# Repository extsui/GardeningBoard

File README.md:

# GardeningBoard
## 概要
- ガーデニングボードは着脱可能基板を自由に抜き差しして自分好みの作品を生み出せるというコンセプトの作品です。
- 当初はガーデニングにちなんで庭関連の基板ばかり作っていましたが、現在はガーデニングという手法をベースにした表現に概念を拡張しています。
  - 系譜：KawaiiMakeMyBoard --> GardeningBoard --> Fountain

## 基板
| 基板名   | 形状                  | 概要                                                                                      | 組み上げ対象作品       |
|----------|-----------------------|-------------------------------------------------------------------------------------------|------------------------|
| Grass    | 草                    | 挿入部品                                                                                  | GardeningBoard 等      |
| Tree     | 木                    | 挿入部品                                                                                  | GardeningBoard 等      |
| House    | 家                    | 挿入部品                                                                                  | GardeningBoard 等      |
| Land     | 正方形 (旧式)・上部側 | 挿入部品用穴付き・半田接合式                                                              | KawaiiMakeMyBoard 専用 |
| Base     | 正方形 (旧式)・下部側 | カードエッジコネクタ土台                                                                  | KawaiiMakeMyBoard 専用 |
| Tile     | 正六角形・上部側      | 挿入部品用穴付き                                                                          | GardeningBoard 等      |
| Ground   | 正六角形・下部側      | STM32F303 使用、Pillar からの信号を挿入分に分配<br>STM 未実装を Base の代わりとしても使用 | GardeningBoard 専用    |
| Pillar   | 正六角形・最下部側    | SeeduinoXIAO 使用、単体動作可、GardeningBoard 制御の最上位                                | GardeningBoard 専用    |
| Building | 縦長長方形・挿入部品  | 7セグ6桁x6行、GardeningBoard と互換性無し                                                 | 新規                   |
| Fountain | 正六角形・下部側      | XIAO-ESP32C3 使用、Building・Tile 想定                                                    | 新規                   |

※順番は開発順

## プログラム
- Firmware/Balan
  - Ground に搭載されている STM32F303 向けのプログラム
  - 上位 I2C から受け取ったデータ (点灯パターン等) を元に、下位 I2C に接続されている HT16K33 を制御する
- M5Stack/Pump
  - PC から USB シリアル経由で受信したデータを Balan に送信する M5Stack 向けのプログラム
  - Balan への送信は I2C に変換して GROVE ケーブル経由で行う
  - GardeningBoard 開発時向けに使用したもので、GardeningBoard 最終系には含まれていない
- Tools/PruningTool
  - Pump と対応する PC 側の制御ツール (C# フォームアプリ)
  - 草/木/家/土等の基本パーツ一つ一つの点灯パターン作成・検討に使用
- Seeedino/Pillar
  - Pillar 基板に搭載されている SeeeduinoXIAO 向けのプログラム
  - PC から USB シリアル経由で受信したデータを Balan に送信する (Pump と立ち位置は似ている)
  - スタンドアローン動作も想定している
  - Pillar 基板に搭載されている以下を制御する
    - タクトスイッチ (状態遷移用)
    - DFPlayerMp3 基板 (音楽再生用)
    - microSD (点灯表示シナリオ読み込み用)
    - ボリューム2個 (輝度調整・表示周期変更用)
    - I2C マスタ GROVE コネクタ (Balan への信号用)
    - 0.96 inch I2C 有機 EL グラフィックス表示器 (各種情報表示用)
- Tools/Sprinkler
  - Pillar と対応する PC 側の制御ツール (C# WPF)
  - PruningTool のように基本パーツの点灯パターン検討も出来なくはないが、<br>Sprinkler はどちらかというと点灯パターンを組み合わせた GardeningBoard 全体の表示シナリオ検討・作成に使用することを想定
  - 表示シナリオ検討は以下の手順で行う
    - GardeningBoard (Pillar) と接続する
    - リアルタイム制御用のテキストボックスにフォーカスを当てた状態にする
    - キーボードのキーそれぞれに各パーツと表示パターンが割り当ててあるので自由にキー入力する
  - 作成した表示シナリオを Pillar で再生できる形式に変換・ファイル出力できる (ハズ)
- Tools/PatternConverter
  - 基本パーツの複雑な点灯パターン検討・作成用の Python スクリプト
  - 点灯パターンは yml ファイルで定義し、以下の二つに変換する
    - C/C++ 形式 (Balan のプログラムに埋め込む用)
    - C# 形式 (Sprinkler のシナリオ検討で点灯パターンを入力補完するためのパターン enum 定義用)
- Tools/BuildingPainter
  - TODO:

※順番は開発順

## 代表的な構成
### KawaiiMakeMyBoard 
| 基板名 | 個数 |
|--------|------|
| Grass  | 2    |
| Tree   | 1    |
| Land   | 1    |
| Base   | 1    |

### GardeningBoard
| 基板名 | 個数 | 備考                        |
|--------|------|-----------------------------|
| Grass  | 3    | 手前側に3個                 |
| Tree   | 3    | 奥側に3個                   |
| House  | 1    | 中央に1個                   |
| Tile   | 7    | -                           |
| Ground | 7    | STM 実装は2個、残りは中継用 |
| Pillar | 1    | 中央基板のさらに下に配置    |

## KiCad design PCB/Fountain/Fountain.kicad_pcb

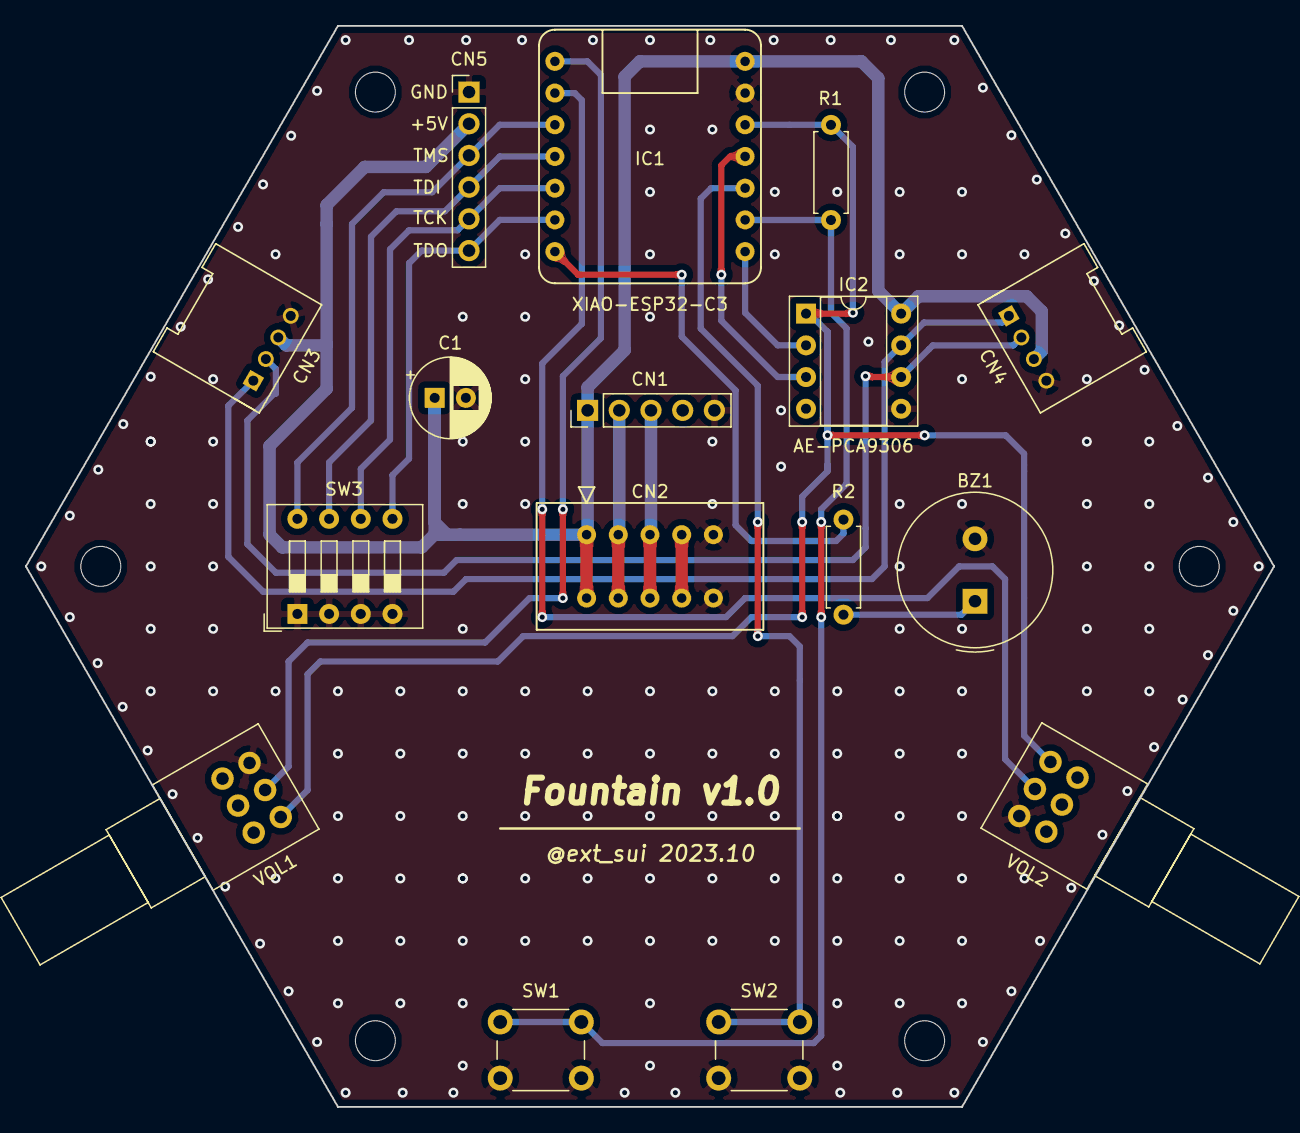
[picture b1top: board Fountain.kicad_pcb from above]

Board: 2 copper layers, 100.0 x 86.6 mm, 22 parts (0 on the bottom side), 17 nets.

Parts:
BZ1: Buzzer; Buzzer_TDK_PS1240P02BT_D12.2mm_H6.5mm
C1: CP; CP_Radial_D6.3mm_P2.50mm
CN1: Conn_01x05_Female; PinHeader_1x05_P2.54mm_Vertical
CN2: CardEdgeConnector5P; CONN_CARD_EDGE_395-010-521-201
CN3, CN4: GROVE_IIC_5V; HW4-2.0-90D
CN5: JTAG; PinHeader_1x06_P2.54mm_Vertical
H1, H2, H3, H4, H5, H6: MountingHole; MountingHole_3.2mm_M3
IC1: XIAO-ESP32-C3; SeeeduinoXIAO
IC2: AE-PCA9306; DIP-8_W7.62mm_Socket
R1: 10k; R_Axial_DIN0207_L6.3mm_D2.5mm_P7.62mm_Horizontal
R2: 1k; R_Axial_DIN0207_L6.3mm_D2.5mm_P7.62mm_Horizontal
SW1, SW2: (TBD); SW_PUSH_6mm_H8.5mm
SW3: DIPSW-4P; SW_DIP_SPSTx04_Slide_9.78x12.34mm_W7.62mm_P2.54mm
VOL1, VOL2: (TBD); Potentiometer_Alps_RK097_Dual_Horizontal

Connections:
3V3: IC1.12, IC2.1, R1.2, VOL1.6, VOL2.6
5V: C1.1, CN1.1, CN2.1, CN3.3, CN4.3, CN5.2, IC1.14, IC2.8
GND: BZ1.2, C1.2, CN1.5, CN2.5, CN3.4, CN4.4, CN5.1, IC1.13, IC2.5, SW1.2, SW2.2, SW3.1, SW3.2, SW3.3, SW3.4, VOL1.4, VOL2.4
unnamed: BZ1.1, R2.2
unnamed: CN5.3, IC1.3, SW3.8
unnamed: CN5.4, IC1.4, SW3.7
unnamed: CN5.5, IC1.5, SW3.6
unnamed: CN5.6, IC1.6, SW3.5
unnamed: IC1.7, R2.1
unnamed: IC1.9, R1.1, SW1.1
unnamed: IC1.10, SW2.1
RV1: IC1.1, VOL1.5
RV2: IC1.2, VOL2.5
SCL_3V3: IC1.8, IC2.2
SCL_5V: CN1.3, CN2.3, CN3.1, CN4.1, IC2.7
SDA_3V3: IC1.11, IC2.3
SDA_5V: CN1.2, CN2.2, CN3.2, CN4.2, IC2.6

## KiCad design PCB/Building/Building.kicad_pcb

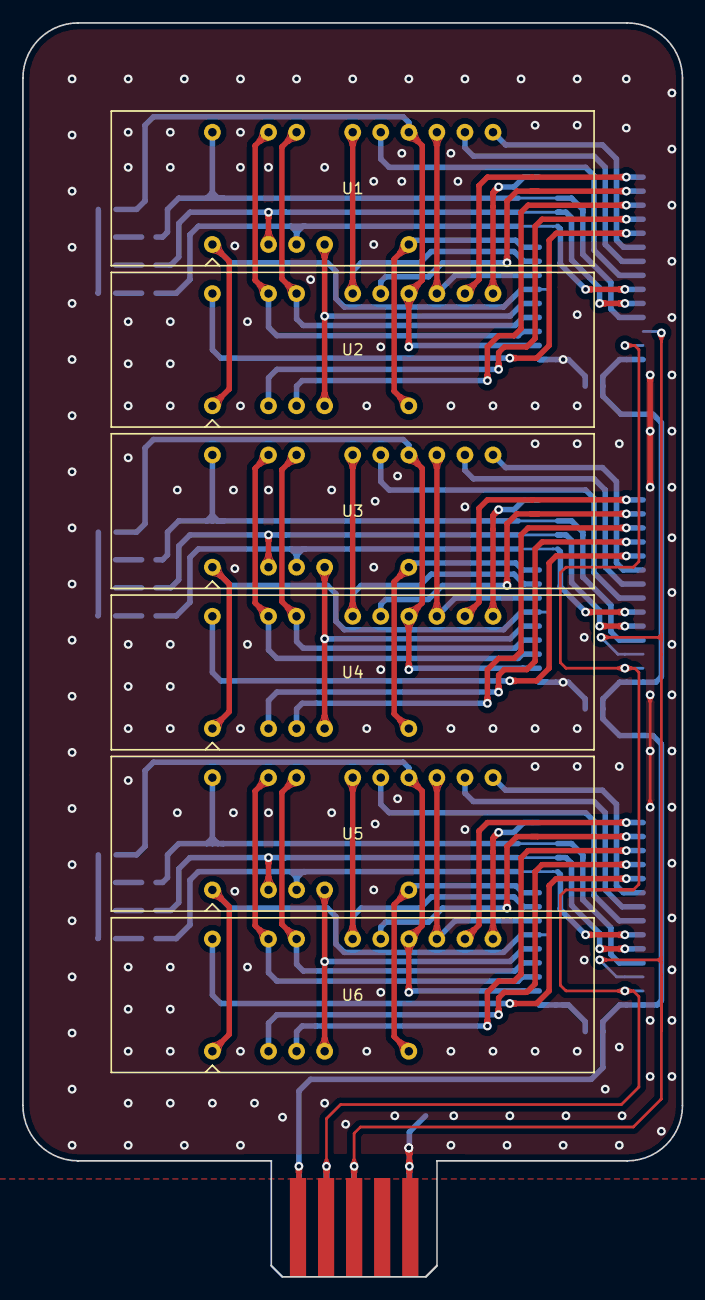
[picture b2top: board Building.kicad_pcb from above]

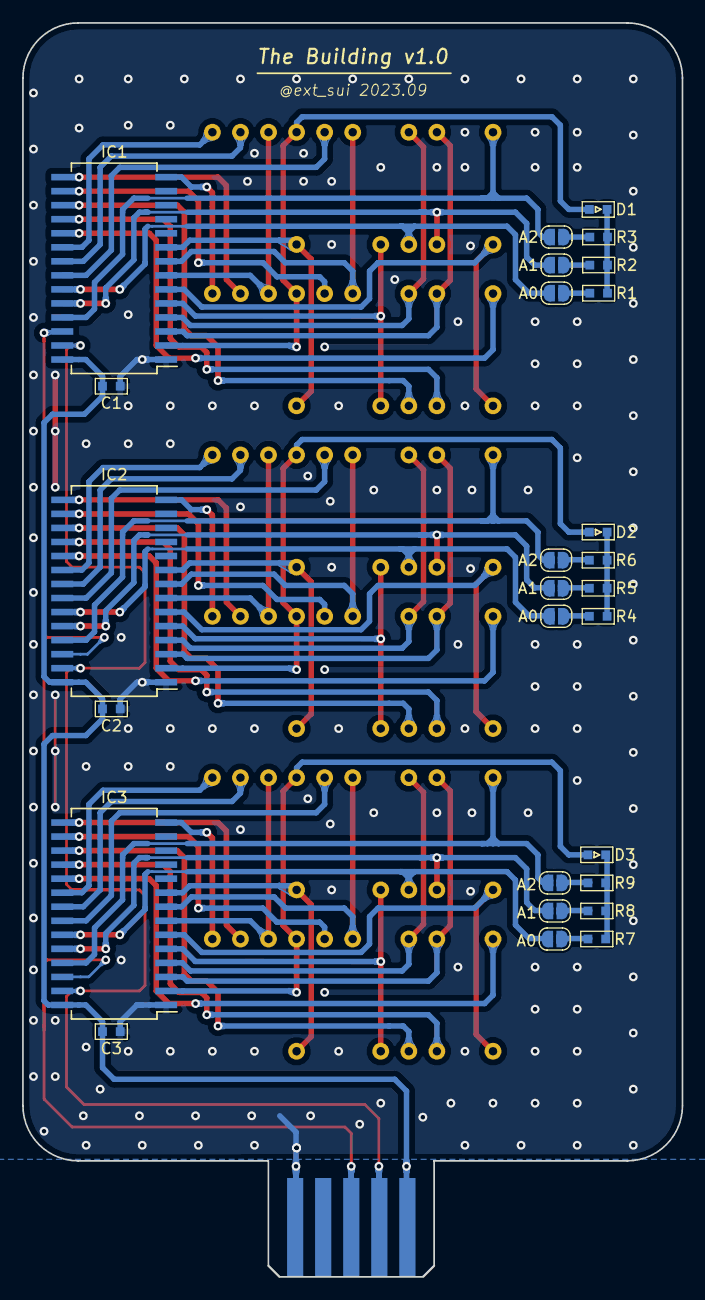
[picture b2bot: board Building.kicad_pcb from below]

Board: 2 copper layers, 59.6 x 113.5 mm, 34 parts (27 on the bottom side), 76 nets.

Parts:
C1, C2, C3: 0.1u; C_1608_HandSolderingCustom
D1, D2, D3: D; LED_1608_HandSolderingCustom
IC1, IC2, IC3: HT16K33-28SOP; SOIC-28W_7.5x18.7mm_P1.27mm
J1: Conn_01x05; EDAC_5P_P2.54mm
JP1, JP4, JP7: A0; SolderJumper-2_P1.3mm_Open_RoundedPad1.0x1.5mm
JP2, JP5, JP8: A1; SolderJumper-2_P1.3mm_Open_RoundedPad1.0x1.5mm
JP3, JP6, JP9: A2; SolderJumper-2_P1.3mm_Open_RoundedPad1.0x1.5mm
R1, R2, R3, R4, R5, R6, R7, R8, R9: 39k; R_1608_HandSolderingCustom
U1, U2, U3, U4, U5, U6: OSL60362_IX; OSL60362_XX

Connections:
+5V: C1.1, C2.1, C3.1, IC1.28, IC2.28, IC3.28, J1.1
/A_1: D1.2, IC1.2, U1.15, U2.15
/A_2: D2.2, IC2.2, U3.15, U4.15
/A_3: D3.2, IC3.2, U5.15, U6.15
/B_1: IC1.3, U1.20, U2.20
/B_2: IC2.3, U3.20, U4.20
/B_3: IC3.3, U5.20, U6.20
/CA1: IC1.25, JP3.2, U1.22
/CA2: IC1.24, JP2.2, U1.3
/CA3: IC1.23, JP1.2, U1.4
/CA4: IC1.22, U1.16
/CA5: IC1.21, U1.13
/CA6: IC1.20, U1.12
/CA7: IC1.19, U2.22
/CA8: IC1.18, U2.3
/CA9: IC1.17, U2.4
/CA10: IC1.16, U2.16
/CA11: IC1.15, U2.13
/CA12: IC1.14, U2.12
/CA13: IC2.25, JP6.2, U3.22
/CA14: IC2.24, JP5.2, U3.3
/CA15: IC2.23, JP4.2, U3.4
/CA16: IC2.22, U3.16
/CA17: IC2.21, U3.13
/CA18: IC2.20, U3.12
/CA19: IC2.19, U4.22
/CA20: IC2.18, U4.3
/CA21: IC2.17, U4.4
/CA22: IC2.16, U4.16
/CA23: IC2.15, U4.13
/CA24: IC2.14, U4.12
/CA25: IC3.25, JP9.2, U5.22
/CA26: IC3.24, JP8.2, U5.3
/CA27: IC3.23, JP7.2, U5.4
/CA28: IC3.22, U5.16
/CA29: IC3.21, U5.13
/CA30: IC3.20, U5.12
/CA31: IC3.19, U6.22
/CA32: IC3.18, U6.3
/CA33: IC3.17, U6.4
/CA34: IC3.16, U6.16
/CA35: IC3.15, U6.13
/CA36: IC3.14, U6.12
/C_1: IC1.4, U1.19, U2.19
/C_2: IC2.4, U3.19, U4.19
/C_3: IC3.4, U5.19, U6.19
/DP_1: IC1.9, U1.8, U2.8
/DP_2: IC2.9, U3.8, U4.8
/DP_3: IC3.9, U5.8, U6.8
/D_1: IC1.5, U1.5, U2.5
/D_2: IC2.5, U3.5, U4.5
/D_3: IC3.5, U5.5, U6.5
/E_1: IC1.6, U1.1, U2.1
/E_2: IC2.6, U3.1, U4.1
/E_3: IC3.6, U5.1, U6.1
/F_1: IC1.7, U1.14, U2.14
/F_2: IC2.7, U3.14, U4.14
/F_3: IC3.7, U5.14, U6.14
/G_1: IC1.8, U1.17, U2.17
/G_2: IC2.8, U3.17, U4.17
/G_3: IC3.8, U5.17, U6.17
GND: C1.2, C2.2, C3.2, IC1.1, IC2.1, IC3.1, J1.5
unnamed: D1.1, R1.2, R2.2, R3.2
unnamed: D2.1, R4.2, R5.2, R6.2
unnamed: D3.1, R7.2, R8.2, R9.2
unnamed: JP1.1, R1.1
unnamed: JP2.1, R2.1
unnamed: JP3.1, R3.1
unnamed: JP4.1, R4.1
unnamed: JP5.1, R5.1
unnamed: JP6.1, R6.1
unnamed: JP7.1, R7.1
unnamed: JP8.1, R8.1
unnamed: JP9.1, R9.1
SCL: IC1.26, IC2.26, IC3.26, J1.3
SDA: IC1.27, IC2.27, IC3.27, J1.2

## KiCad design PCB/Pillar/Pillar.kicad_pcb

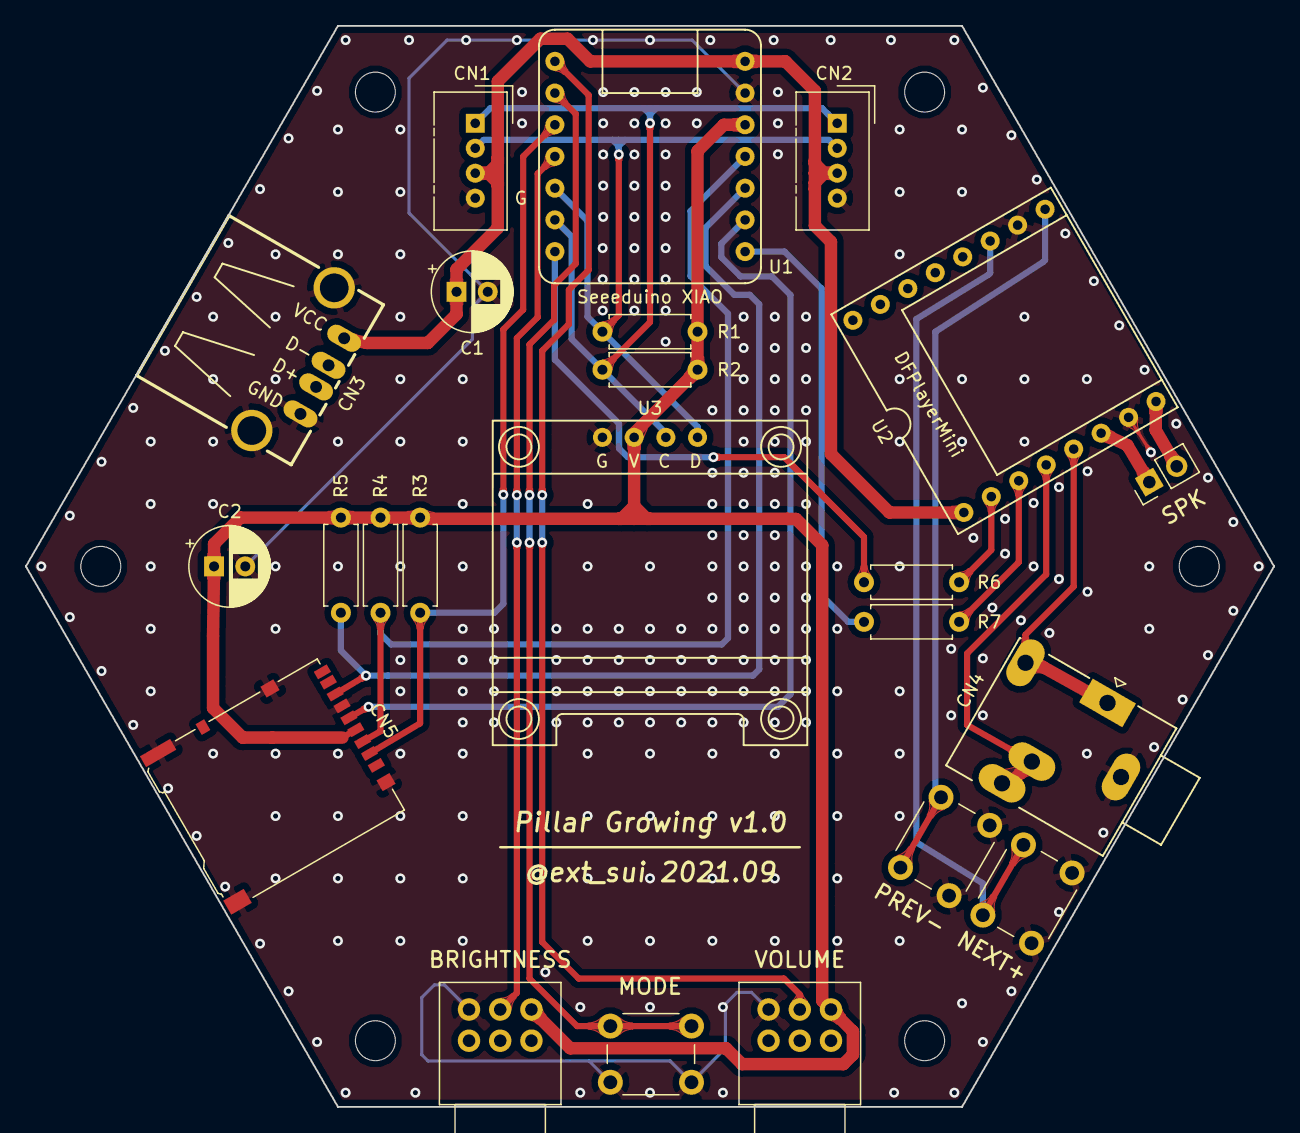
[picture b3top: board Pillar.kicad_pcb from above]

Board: 2 copper layers, 100.0 x 86.6 mm, 29 parts (0 on the bottom side), 22 nets.

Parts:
C1, C2: 100u; CP_Radial_D6.3mm_P2.50mm
CN1, CN2: GROVE_IIC_5V; NS-Tech_Grove_1x04_P2mm_Vertical
CN3: USB_A; USB4+2P-2.0-90D
CN4: AudioJack3_SwitchTR; Jack_3.5mm_Ledino_KB3SPRS_Horizontal
CN5: Micro_SD_Card_Det_Hirose_DM3AT; microSD_HC_Hirose_DM3AT-SF-PEJM5
H1, H2, H3, H4, H5, H6: MountingHole; MountingHole_3.2mm_M3
J1: Speaker; PinHeader_1x02_P2.54mm_Vertical
R1, R2, R3, R4, R5: 4.7k; R_Axial_DIN0207_L6.3mm_D2.5mm_P7.62mm_Horizontal
R6, R7: 1k; R_Axial_DIN0207_L6.3mm_D2.5mm_P7.62mm_Horizontal
RV1: BRIGHTNESS; Potentiometer_Alps_RK097_Dual_Horizontal
RV2: VOLUME; Potentiometer_Alps_RK097_Dual_Horizontal
SW1: MDOE; SW_PUSH_6mm_H8.5mm
SW2: NEXT/VOL+; SW_PUSH_6mm_H8.5mm
SW3: PREV/VOL-; SW_PUSH_6mm_H8.5mm
U1: SeeeduinoXIAO
U2: DFPlayerMini
U3: OLED_128x64_IIC; OLED_128x64_0.96inch

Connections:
3V3: C2.1, CN5.4, R1.1, R2.1, R3.1, R4.1, R5.1, RV1.6, RV2.6, U1.12, U3.2
5V: C1.1, CN1.3, CN2.3, CN3.1, U1.14, U2.1
CS: CN5.2, R3.2, U1.3
GND: C1.2, C2.2, CN1.4, CN2.4, CN3.4, CN3.5, CN4.S, CN5.6, CN5.11, RV1.4, RV2.4, SW1.2, SW2.2, SW3.2, U1.13, U2.7, U2.10, U3.1
MISO: CN5.7, R5.2, U1.10
MOSI: CN5.3, R4.2, U1.11
unnamed: CN4.R, CN4.RN, U2.4
unnamed: CN4.T, CN4.TN, U2.5
unnamed: J1.1, U2.6
unnamed: J1.2, U2.8
unnamed: R6.1, U2.2
unnamed: R7.1, U2.3
unnamed: SW1.1, U1.2
unnamed: SW2.1, U2.11
unnamed: SW3.1, U2.9
RV_B: RV1.5, U1.4
RV_V: RV2.5, U1.1
RXD: R7.2, U1.8
SCK: CN5.5, U1.9
SCL: CN1.1, CN2.1, R2.2, U1.6, U3.3
SDA: CN1.2, CN2.2, R1.2, U1.5, U3.4
TXD: R6.2, U1.7

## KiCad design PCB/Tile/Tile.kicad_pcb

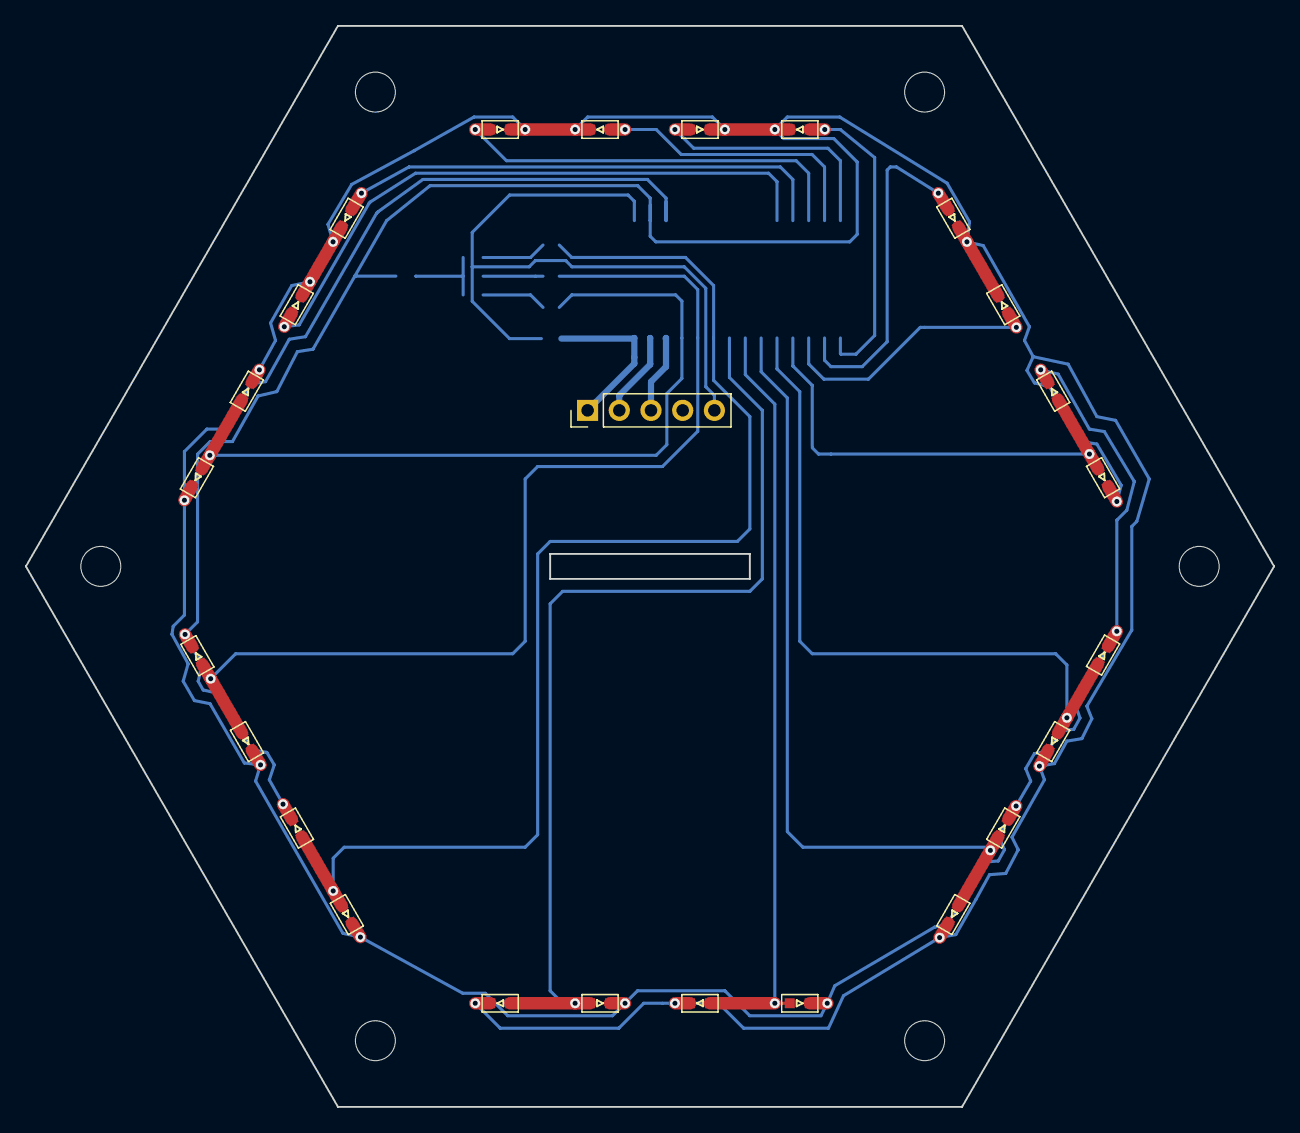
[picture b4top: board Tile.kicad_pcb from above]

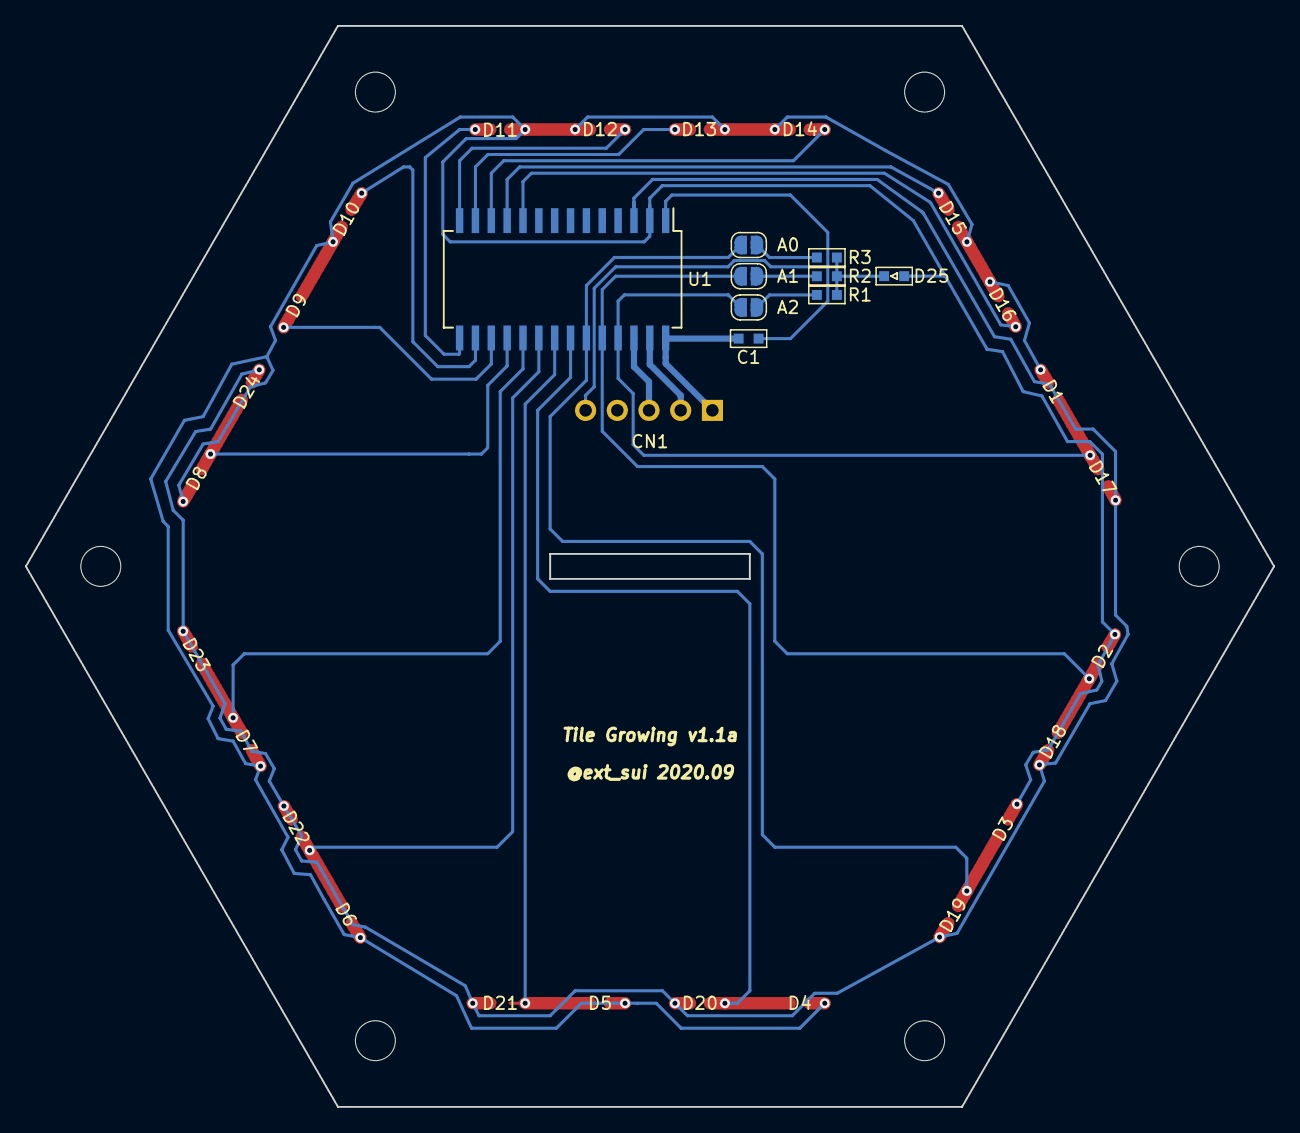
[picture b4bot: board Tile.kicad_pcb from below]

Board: 2 copper layers, 100.0 x 86.6 mm, 40 parts (9 on the bottom side), 26 nets.

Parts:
A0: A0; SolderJumper-2_P1.3mm_Open_RoundedPad1.0x1.5mm
A1: A1; SolderJumper-2_P1.3mm_Open_RoundedPad1.0x1.5mm
A2: A2; SolderJumper-2_P1.3mm_Open_RoundedPad1.0x1.5mm
C1: 0.1u; C_1608_HandSolderingCustom
CN1: Conn_01x05_Male; PinHeader_1x05_P2.54mm_Vertical
D1, D2, D3, D4, D5, D6, D7, D8, D9, D10, D11, D12, D13, D14, D15, D16, D17, D18, D19, D20, D21, D22, D23, D24: LED; LED_1608_HandSolderingCustom
D25: D; LED_1608_HandSolderingCustom
H1, H2, H3, H4, H5, H6: MountingHole; MountingHole_3.2mm_M3
R1, R2, R3: 39k; R_1608_HandSolderingCustom
U1: HT16K33-28SOP; SOIC-28W_7.5x18.7mm_P1.27mm

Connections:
+5V: C1.1, CN1.1, U1.28
GND: C1.2, CN1.5, U1.1
unnamed: D1.1, D2.1, D3.1, D4.1, D5.1, D6.1, D7.1, D8.1, D9.1, D10.1, D11.1, D12.1, D13.1, D14.1, D15.1, D16.1, D25.2, U1.2
unnamed: A2.2, D1.2, D17.2, U1.25
unnamed: D9.2, U1.17
unnamed: D10.2, U1.16
unnamed: D11.2, U1.15
unnamed: D12.2, U1.14
unnamed: D13.2, U1.13
unnamed: D14.2, U1.12
unnamed: D15.2, U1.11
unnamed: D16.2, U1.10
unnamed: D17.1, D18.1, D19.1, D20.1, D21.1, D22.1, D23.1, D24.1, U1.3
unnamed: A1.2, D2.2, D18.2, U1.24
unnamed: A0.2, D3.2, D19.2, U1.23
unnamed: D4.2, D20.2, U1.22
unnamed: D5.2, D21.2, U1.21
unnamed: D6.2, D22.2, U1.20
unnamed: D7.2, D23.2, U1.19
unnamed: D8.2, D24.2, U1.18
unnamed: D25.1, R1.2, R2.2, R3.2
unnamed: A2.1, R1.1
unnamed: A1.1, R2.1
unnamed: A0.1, R3.1
SCL: CN1.3, U1.26
SDA: CN1.2, U1.27

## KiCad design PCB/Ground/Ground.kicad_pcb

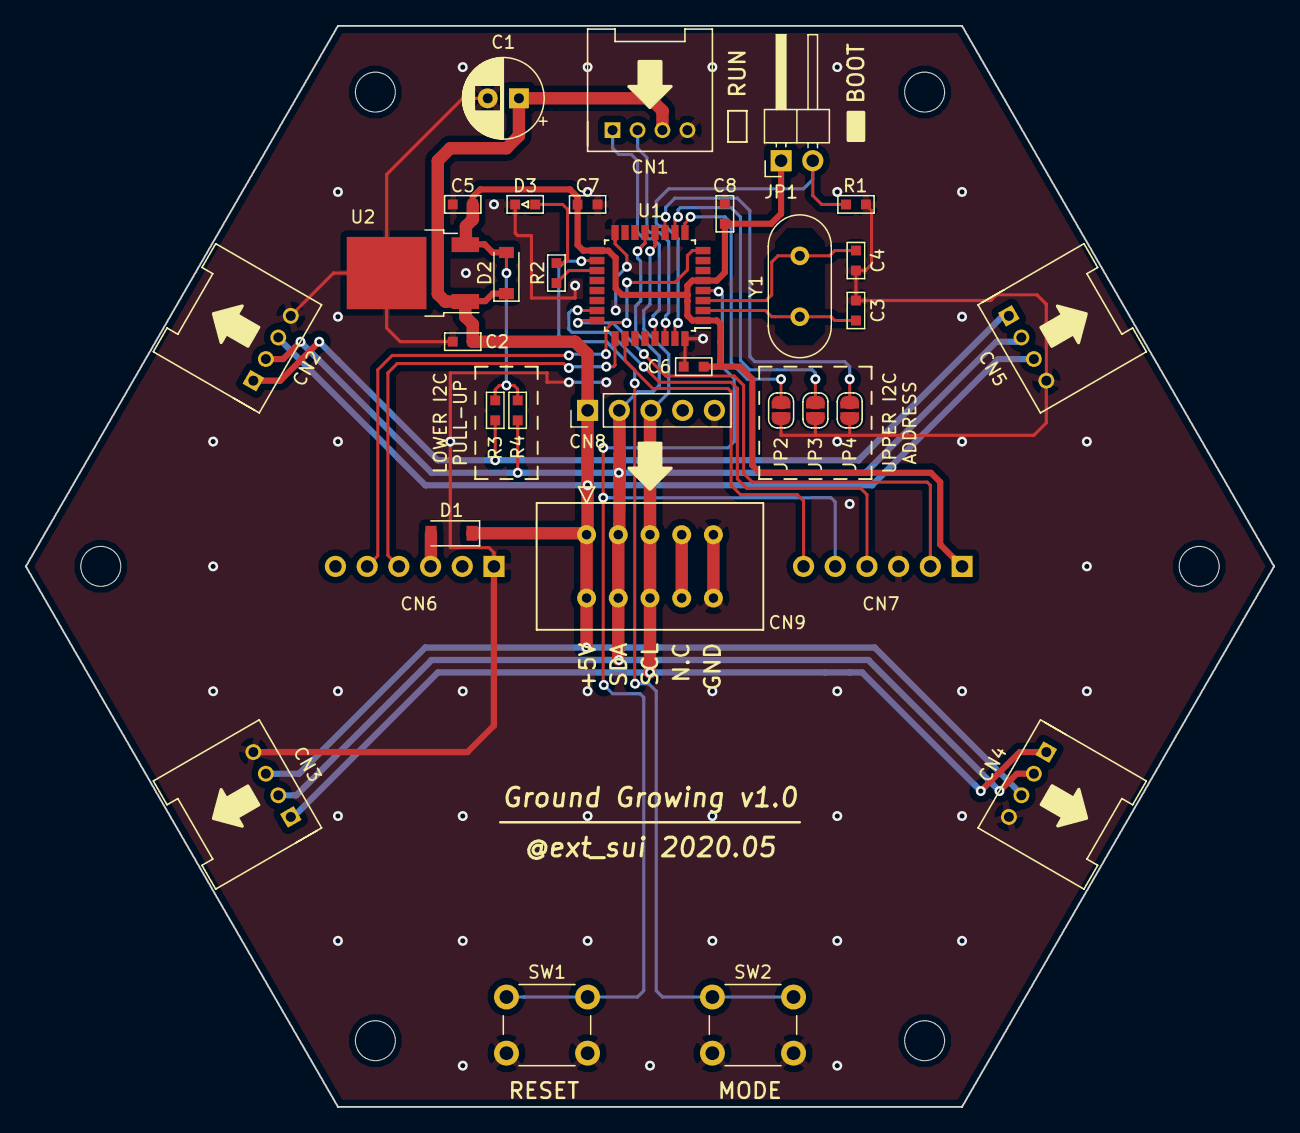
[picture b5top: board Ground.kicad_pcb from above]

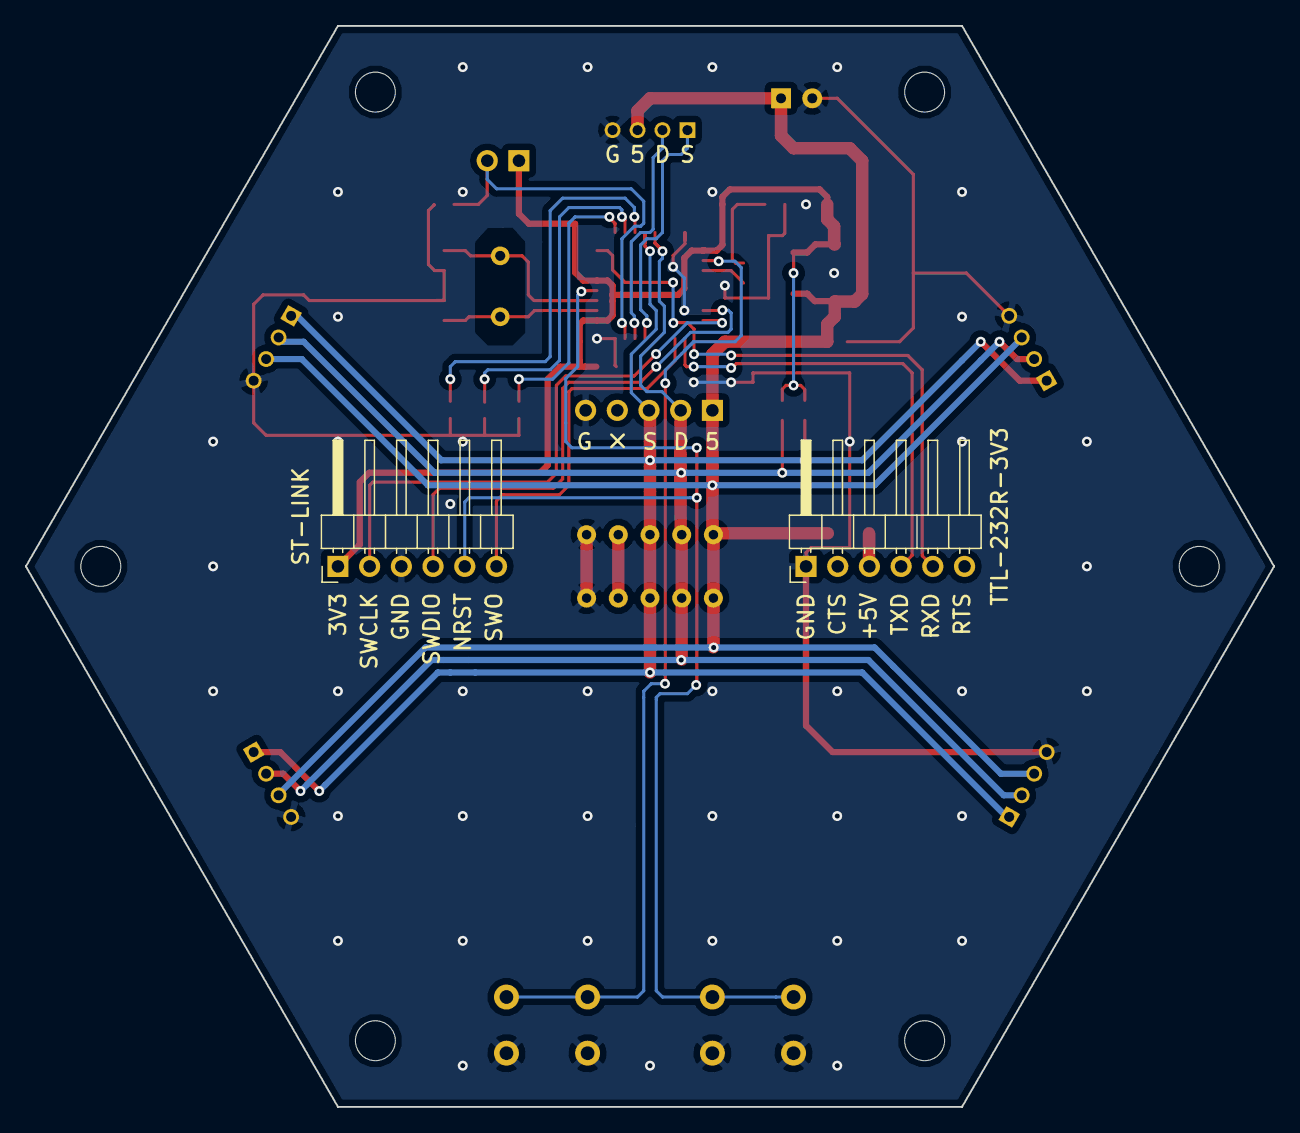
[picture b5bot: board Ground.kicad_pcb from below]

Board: 2 copper layers, 100.0 x 86.6 mm, 39 parts (2 on the bottom side), 23 nets.

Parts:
C1: 47uF; CP_Radial_D6.3mm_P2.50mm
C2: 0.1uF; C_1608_HandSolderingCustom
C3, C4: 22pF; C_1608_HandSolderingCustom
C5: 10uF; C_1608_HandSolderingCustom
C6, C7, C8: 0.1u; C_1608_HandSolderingCustom
CN1, CN2, CN3, CN4, CN5: GROVE; HW4-2.0-90D
CN6: TTL-232R-3V3; PinHeader_1x06_P2.54mm_Horizontal
CN7: ST-LINK; PinHeader_1x06_P2.54mm_Horizontal
CN8: Conn_01x05_Female; PinHeader_1x05_P2.54mm_Vertical
CN9: CardEdgeConnector5P; CONN_CARD_EDGE_395-010-521-201
D1, D2: SS2040FL; D_SOD-123
D3: LED; LED_1608_HandSolderingCustom
H1, H2, H3, H4, H5, H6: MountingHole; MountingHole_3.2mm_M3
JP1: JP_BOOT; PinHeader_1x02_P2.54mm_Horizontal
JP2, JP3, JP4: Jumper_NO_Small; SolderJumper-2_P1.3mm_Open_RoundedPad1.0x1.5mm
R1, R2, R3, R4: 10k; C_1608_HandSolderingCustom
SW1: RESET; SW_PUSH_6mm_H8mm
SW2: MODE; SW_PUSH_6mm_H8mm
U1: STM32F303K8T6; LQFP-32_7x7mm_P0.8mm
U2: NJM2845DL1-33; TO-252-2
Y1: 8MHz; Crystal_HC49-4H_Vertical

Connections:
3V3: C5.1, C6.2, C7.2, C8.2, CN7.1, D2.2, JP1.1, R3.1, R4.1, U1.1, U1.5, U1.17, U2.3
5V: C1.1, C2.1, CN1.3, CN2.3, CN3.3, CN4.3, CN5.3, CN8.1, CN9.1, D1.1, D2.1, U2.1
GND: C1.2, C2.2, C3.2, C4.2, C5.2, C6.1, C7.1, C8.1, CN1.4, CN2.4, CN3.4, CN4.4, CN5.4, CN6.1, CN7.3, CN8.5, CN9.5, D3.1, JP2.1, JP3.1, JP4.1, R1.2, SW1.1, SW2.2, U1.16, U1.32, U2.2
LOWER_SCL: CN2.1, CN3.1, CN4.1, CN5.1, CN8.3, CN9.3, R3.2, U1.12
LOWER_SDA: CN2.2, CN3.2, CN4.2, CN5.2, CN8.2, CN9.2, R4.2, U1.13
NRST: CN7.5, SW1.2, U1.4
unnamed: C3.1, U1.2, Y1.1
unnamed: C4.1, U1.3, Y1.2
unnamed: CN6.3, D1.2
unnamed: D3.2, R2.2
unnamed: JP1.2, R1.1, U1.31
unnamed: JP2.2, U1.9
unnamed: JP3.2, U1.10
unnamed: JP4.2, U1.11
unnamed: R2.1, U1.19
unnamed: SW2.1, U1.18
RXD: CN6.5, U1.8
SWCLK: CN7.2, U1.24
SWDIO: CN7.4, U1.23
SWO: CN7.6, U1.26
TXD: CN6.4, U1.25
UPPER_SCL: CN1.1, U1.29
UPPER_SDA: CN1.2, U1.30

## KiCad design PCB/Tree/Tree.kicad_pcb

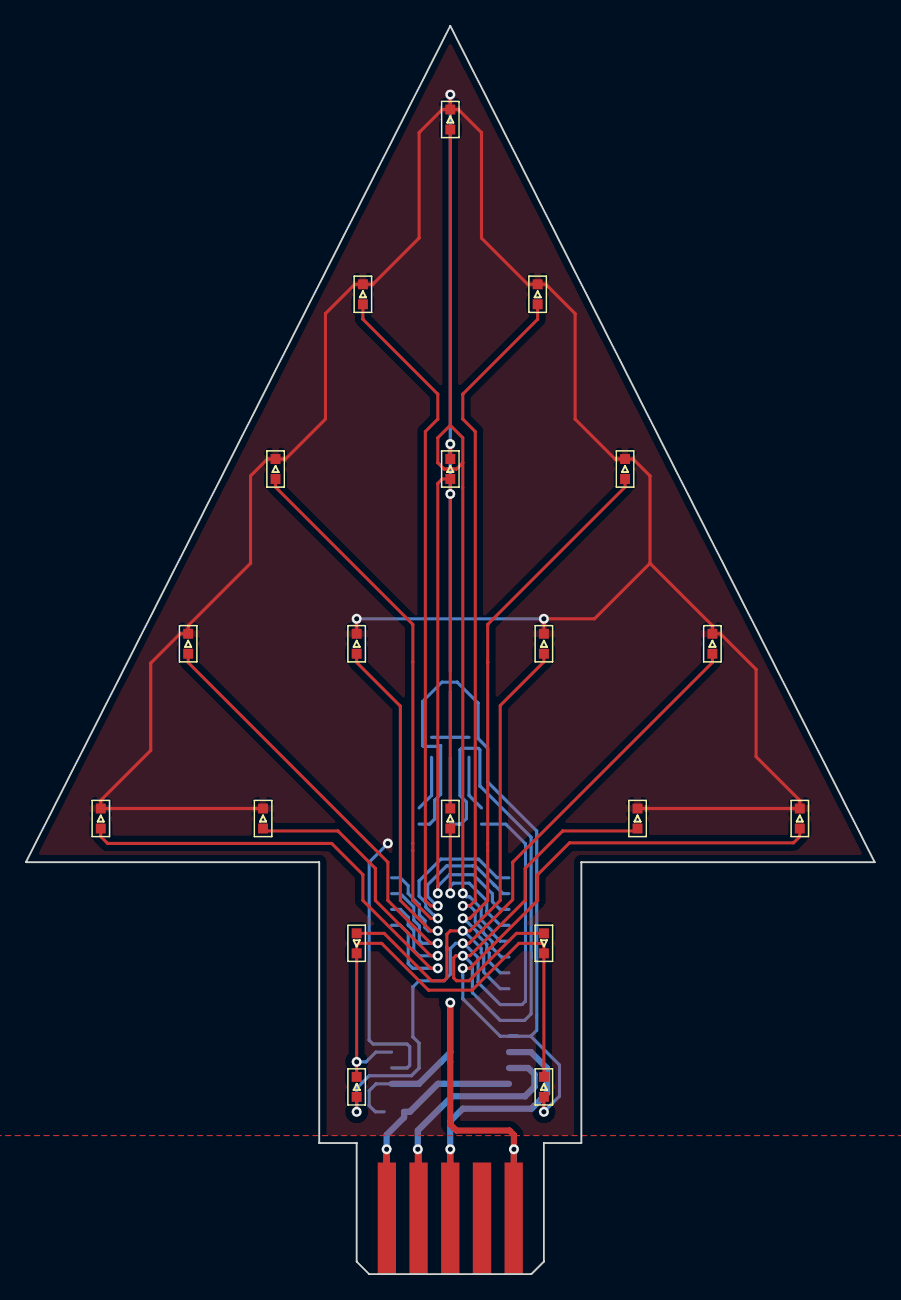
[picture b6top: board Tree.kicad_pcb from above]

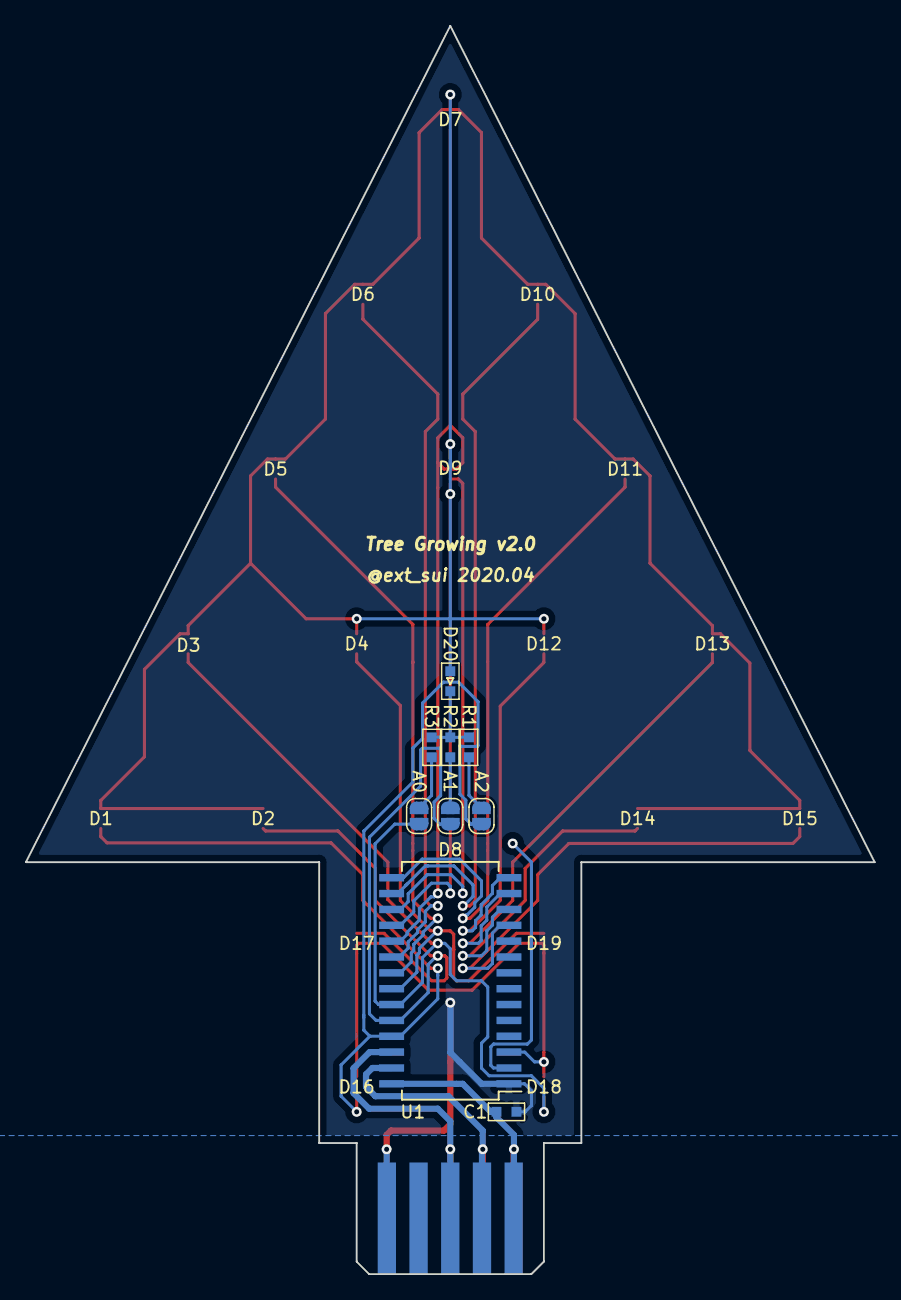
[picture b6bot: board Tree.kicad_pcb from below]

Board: 2 copper layers, 68.0 x 100.0 mm, 29 parts (9 on the bottom side), 25 nets.

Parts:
C1: 0.1u; C_1608_HandSolderingCustom
D1, D2, D3, D4, D5, D6, D7, D8, D9, D10, D11, D12, D13, D14, D15, D16, D17, D18, D19: LED; LED_1608_HandSolderingCustom
D20: D; LED_1608_HandSolderingCustom
J1: Conn_01x05; EDAC_5P_P2.54mm
JP1: A2; SolderJumper-2_P1.3mm_Open_RoundedPad1.0x1.5mm
JP2: A1; SolderJumper-2_P1.3mm_Open_RoundedPad1.0x1.5mm
JP3: A0; SolderJumper-2_P1.3mm_Open_RoundedPad1.0x1.5mm
R1, R2, R3: 39k; R_1608_HandSolderingCustom
U1: HT16K33-28SOP; SOIC-28W_7.5x18.7mm_P1.27mm

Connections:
+5V: C1.1, J1.1, U1.28
GND: C1.2, J1.5, U1.1
unnamed: D1.1, D2.1, D3.1, D4.1, D5.1, D6.1, D7.1, D8.1, D9.1, D10.1, D11.1, D12.1, D13.1, D14.1, D15.1, D20.2, U1.2
unnamed: D1.2, D16.2, JP1.2, U1.25
unnamed: D5.2, U1.21
unnamed: D6.2, U1.20
unnamed: D7.2, U1.19
unnamed: D8.2, U1.18
unnamed: D9.2, U1.17
unnamed: D10.2, U1.16
unnamed: D11.2, U1.15
unnamed: D12.2, U1.14
unnamed: D13.2, U1.13
unnamed: D14.2, U1.12
unnamed: D15.2, U1.11
unnamed: D16.1, D17.1, D18.1, D19.1, U1.3
unnamed: D2.2, D17.2, JP2.2, U1.24
unnamed: D3.2, D18.2, JP3.2, U1.23
unnamed: D4.2, D19.2, U1.22
unnamed: D20.1, R1.2, R2.2, R3.2
unnamed: JP1.1, R1.1
unnamed: JP2.1, R2.1
unnamed: JP3.1, R3.1
SCL: J1.3, U1.26
SDA: J1.2, U1.27

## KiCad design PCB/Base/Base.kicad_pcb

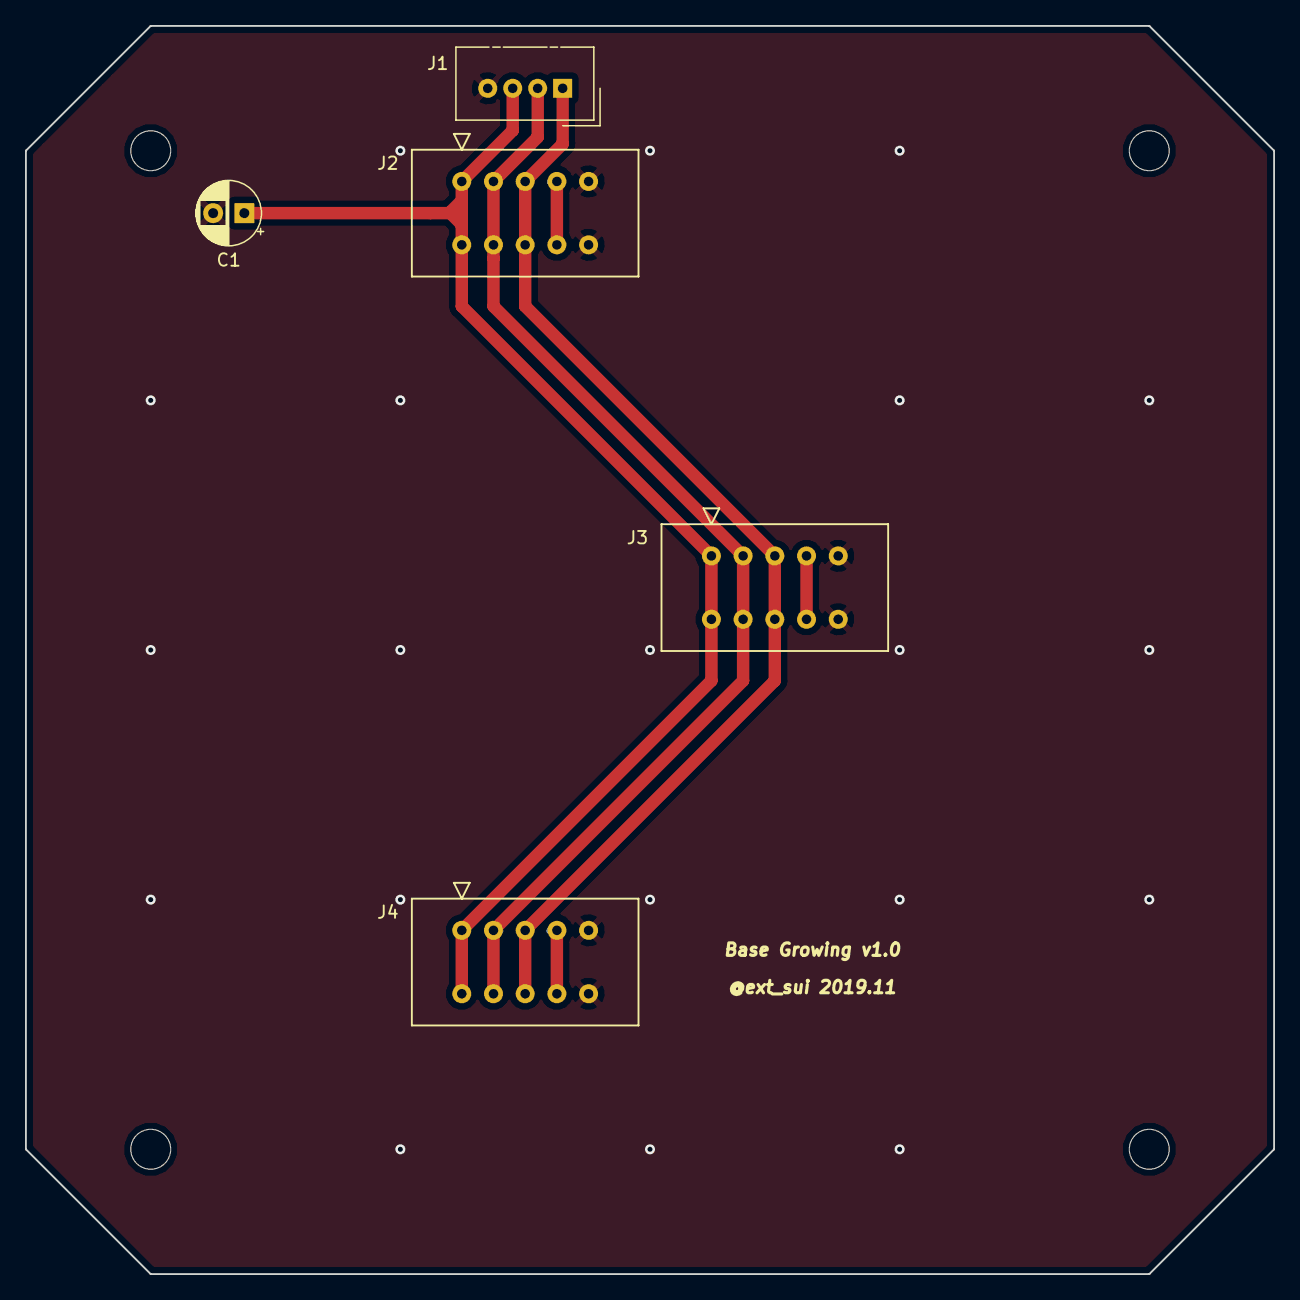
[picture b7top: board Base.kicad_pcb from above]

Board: 2 copper layers, 100.0 x 100.0 mm, 9 parts (0 on the bottom side), 4 nets.

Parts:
C1: 10u; CP_Radial_D5.0mm_P2.50mm
J1: Conn_01x04; NS-Tech_Grove_1x04_P2mm_Vertical
J2, J3, J4: Conn_01x05; CONN_CARD_EDGE_395-010-521-201
REF1, REF2, REF3, REF4: MountingHole_3.2mm_M3

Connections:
+5V: C1.1, J1.3, J2.1, J3.1, J4.1
GND: C1.2, J1.4, J2.5, J3.5, J4.5
SCL: J1.1, J2.3, J3.3, J4.3
SDA: J1.2, J2.2, J3.2, J4.2
